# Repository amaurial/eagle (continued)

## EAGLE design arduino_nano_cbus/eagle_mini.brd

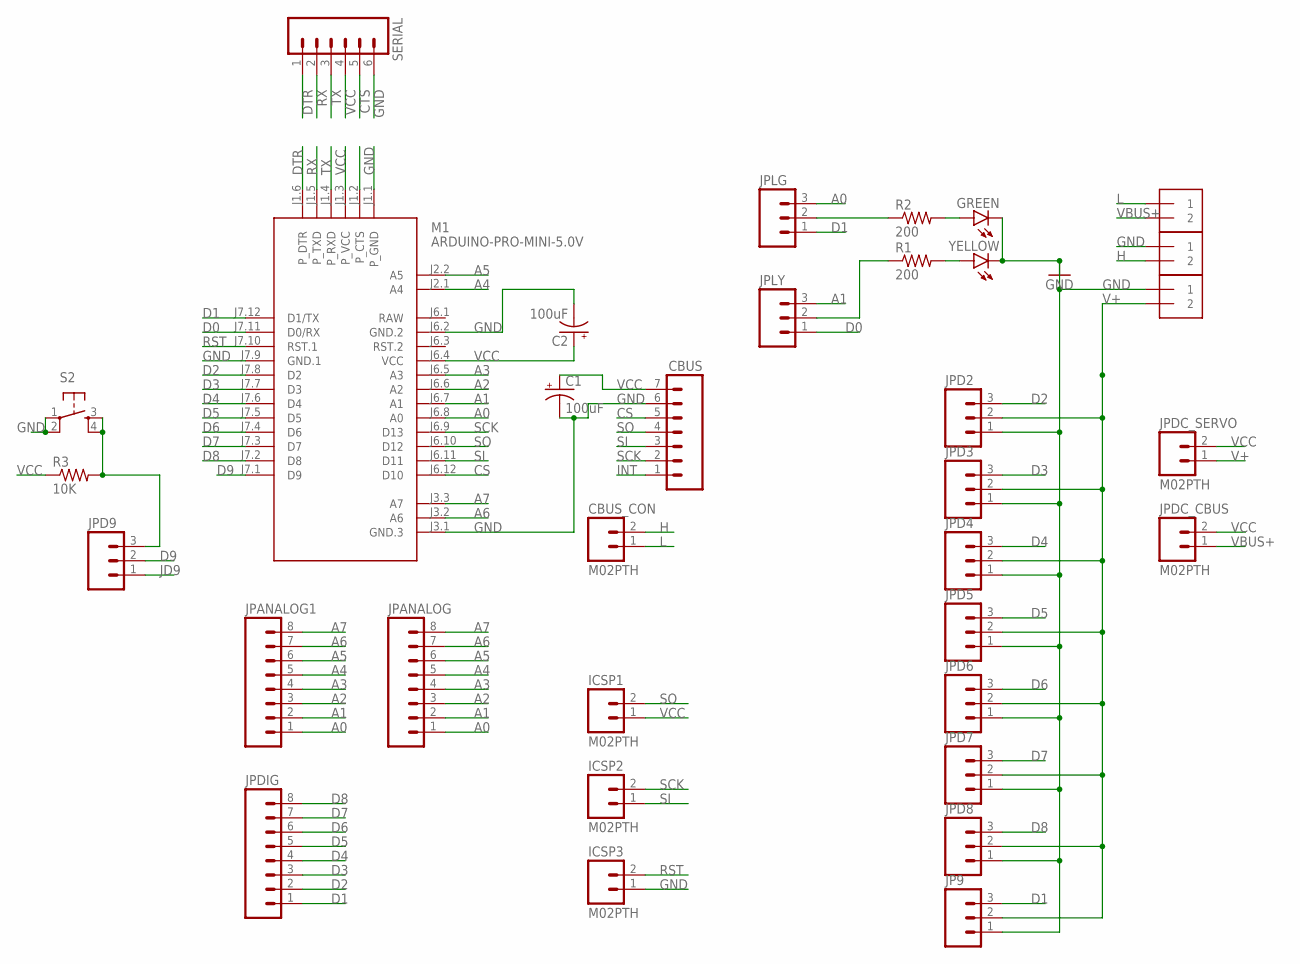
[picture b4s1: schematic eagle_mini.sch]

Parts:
C1, C2: 100uF; E2,5-6
CBUS: M07; 1X07
CBUS_CON: M02PTH; 1X02
EXT_VCC: 1X2-3.5MM
GREEN: LED-3MM-NO_SILK; LED3MM-NS
ICSP1, ICSP2, ICSP3: M02PTH; 1X02
J1, J2: 1X2-3.5MM
JP9: M03PTH; 1X03
JPANALOG, JPANALOG1: M08; 1X08_ROUND
JPD2, JPD3, JPD4, JPD5, JPD6, JPD7, JPD8, JPD9: M03PTH; 1X03
JPDC_CBUS: M02PTH; 1X02
JPDC_SERVO: M02PTH; 1X02
JPDIG: M08; 1X08_ROUND
JPLG: M03PTH; 1X03
JPLY: M03PTH; 1X03
M1: ARDUINO-PRO-MINI-5.0V; ARDUINO-PRO-MINI
R1, R2: 200; AXIAL-0.3
R3: 10K; AXIAL-0.3
S2: TAC_SWITCHPTH; TACTILE-PTH
SERIAL: M06SILK_FEMALE_PTH; 1X06
YELLOW: LED-3MM-NO_SILK; LED3MM-NS

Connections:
A0: JPANALOG.1, JPANALOG1.1, JPLG.3, M1.J6.8 (A0)
A1: JPANALOG.2, JPANALOG1.2, JPLY.3, M1.J6.7 (A1)
A2: JPANALOG.3, JPANALOG1.3, M1.J6.6 (A2)
A3: JPANALOG.4, JPANALOG1.4, M1.J6.5 (A3)
A4: JPANALOG.5, JPANALOG1.5, M1.J2.1 (A4)
A5: JPANALOG.6, JPANALOG1.6, M1.J2.2 (A5)
A6: JPANALOG.7, JPANALOG1.7, M1.J3.2 (A6)
A7: JPANALOG.8, JPANALOG1.8, M1.J3.3 (A7)
CS: CBUS.5, M1.J6.12 (D10)
CTS: SERIAL.5
D0: JPLY.1, M1.J7.11 (D0/RX)
D1: JP9.3, JPDIG.1, JPLG.1, M1.J7.12 (D1/TX)
D2: JPD2.3, JPDIG.2, M1.J7.8 (D2)
D3: JPD3.3, JPDIG.3, M1.J7.7 (D3)
D4: JPD4.3, JPDIG.4, M1.J7.6 (D4)
D5: JPD5.3, JPDIG.5, M1.J7.5 (D5)
D6: JPD6.3, JPDIG.6, M1.J7.4 (D6)
D7: JPD7.3, JPDIG.7, M1.J7.3 (D7)
D8: JPD8.3, JPDIG.8, M1.J7.2 (D8)
D9: JPD9.2, M1.J7.1 (D9)
DTR: M1.J1.6 (P_DTR), SERIAL.1
GND: C1.-, C2.-, CBUS.6, EXT_VCC.1, GREEN.K (C), ICSP3.1, J1.1, JP9.1, JPD2.1, JPD3.1, JPD4.1, JPD5.1, JPD6.1, JPD7.1, JPD8.1, M1.J1.1 (P_GND), M1.J3.1 (GND.3), M1.J6.2 (GND.2), M1.J7.9 (GND.1), S2.1, S2.2, SERIAL.6, YELLOW.K (C)
H: CBUS_CON.2, J1.2
INT: CBUS.1
JD9: JPD9.1
L: CBUS_CON.1, J2.1
unnamed: JPD9.3, R3.P$2 (2), S2.3, S2.4
unnamed: GREEN.A, R2.P$2 (2)
unnamed: R1.P$2 (2), YELLOW.A
unnamed: JPLG.2, R2.P$1 (1)
unnamed: JPLY.2, R1.P$1 (1)
RAW: M1.J6.1 (RAW)
RST: ICSP3.2, M1.J7.10 (RST.1)
RX: M1.J1.5 (P_TXD), SERIAL.2
SCK: CBUS.2, ICSP2.2, M1.J6.9 (D13)
SI: CBUS.3, ICSP2.1, M1.J6.11 (D11)
SO: CBUS.4, ICSP1.2, M1.J6.10 (D12)
TX: M1.J1.4 (P_RXD), SERIAL.3
V+: EXT_VCC.2, JP9.2, JPD2.2, JPD3.2, JPD4.2, JPD5.2, JPD6.2, JPD7.2, JPD8.2, JPDC_SERVO.1
VBUS+: J2.2, JPDC_CBUS.1
VCC: C1.+, C2.+, CBUS.7, ICSP1.1, JPDC_CBUS.2, JPDC_SERVO.2, M1.J1.3 (P_VCC), M1.J6.4 (VCC), R3.P$1 (1), SERIAL.4

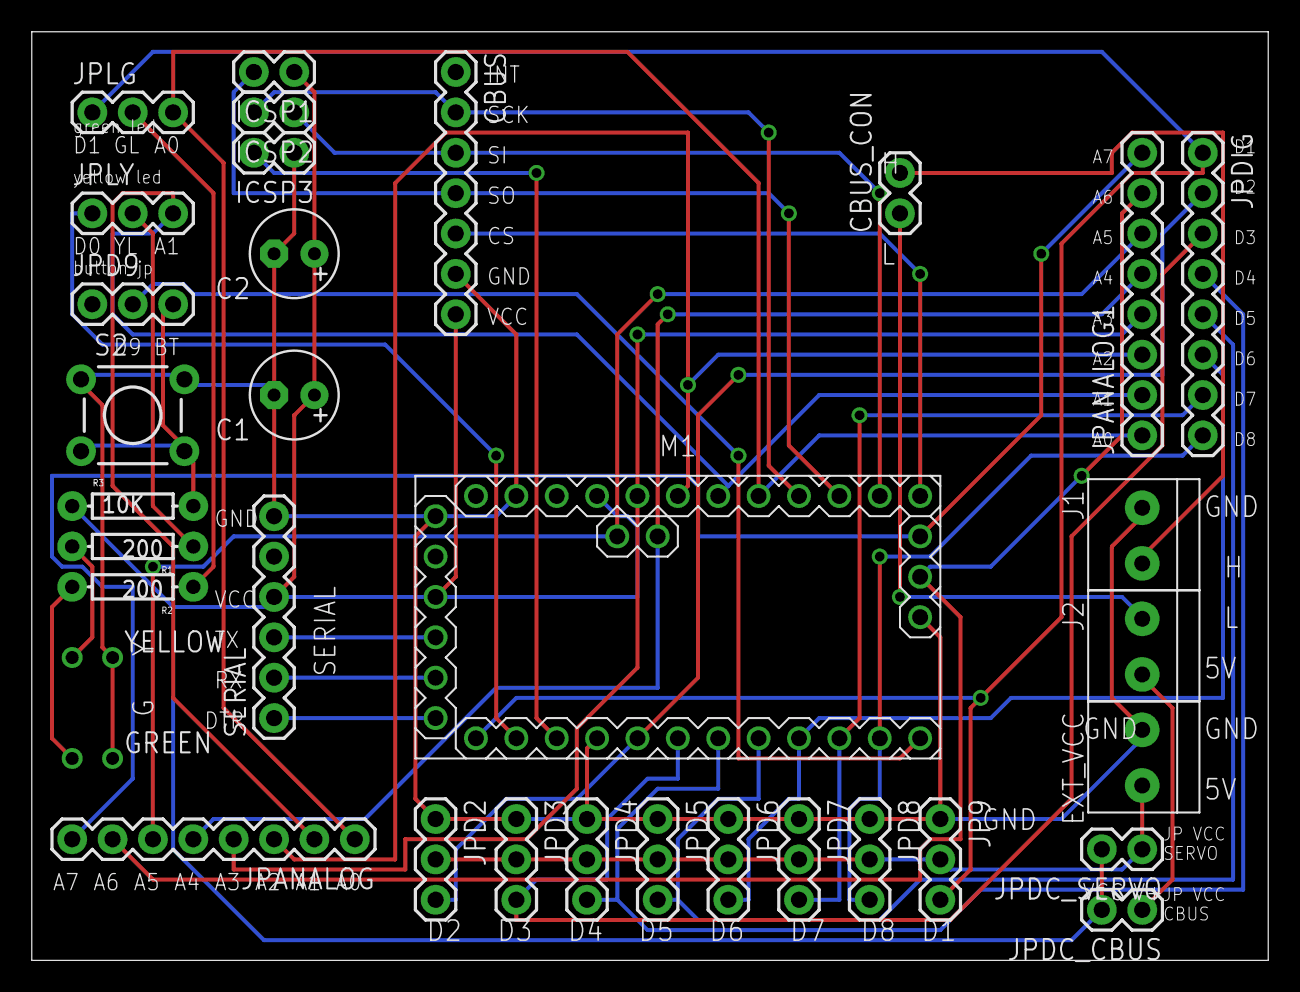
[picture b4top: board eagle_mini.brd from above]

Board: 2 copper layers, 77.8 x 58.4 mm, 34 parts (0 on the bottom side), 37 nets.

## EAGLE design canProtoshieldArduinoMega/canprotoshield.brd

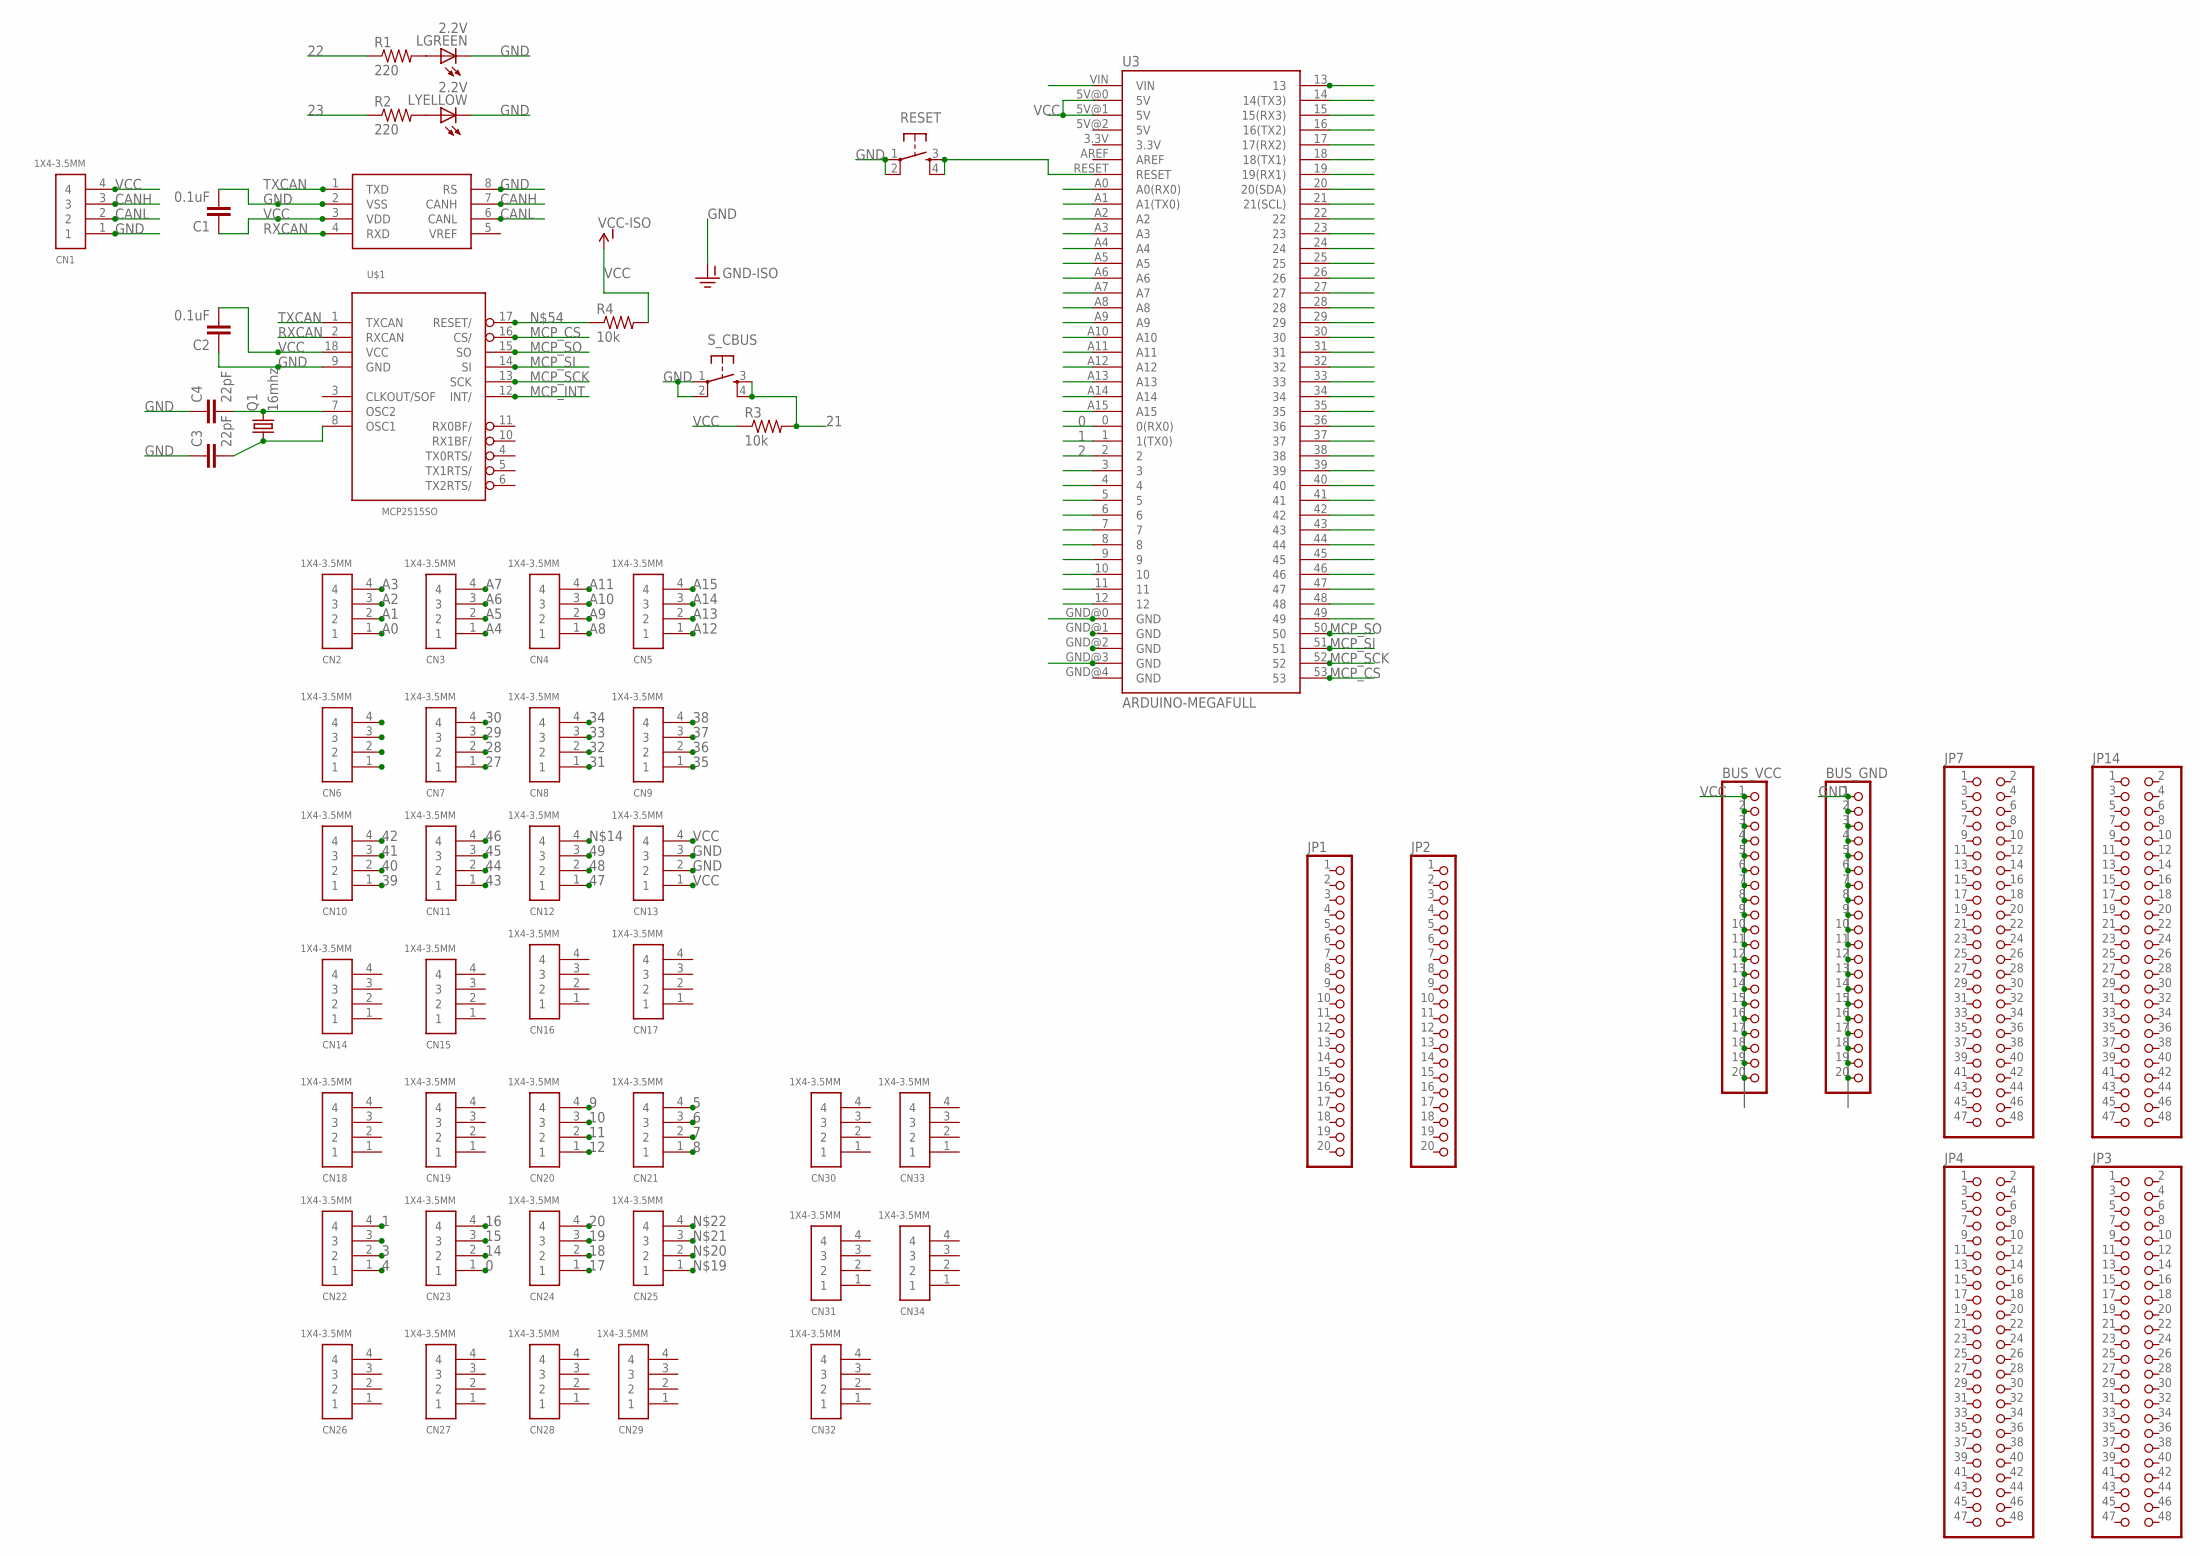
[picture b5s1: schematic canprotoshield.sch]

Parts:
BUS_GND: PINHD-1X20; 1X20
BUS_VCC: PINHD-1X20; 1X20
C1, C2: 0.1uF; 0805
C3, C4: 22pF; 0805
CN1, CN2, CN3, CN4, CN5, CN6, CN7, CN8, CN9, CN10, CN11, CN12, CN13, CN14, CN15, CN16, CN17, CN18, CN19, CN20, CN21, CN22, CN23, CN24, CN25, CN26, CN27, CN28, CN29, CN30, CN31, CN32, CN33, CN34: 1X4-3.5MM; 1X04-3.5MM
JP1, JP2: PINHD-1X20-BIG; 1X20-BIG
JP3, JP4, JP7, JP14: PINHD-2X24; 2X24
LGREEN: 2.2V; LED3MM
LYELLOW: 2.2V; LED3MM
Q1: 16mhz; HC49/S
R1, R2: 220; M2012
R3, R4: 10k; M2012
RESET: TAC_SWITCHPTH; TACTILE-PTH
S_CBUS: TAC_SWITCHPTH; TACTILE-PTH
U2: MCP2551; SO08
U3: ARDUINO-MEGAFULL; ARDUINO_MEGA
U$1: MCP2515SO; SO18L

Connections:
0: CN23.1, U3.0 (0(RX0))
1: CN22.4, U3.1 (1(TX0))
2: CN22.3, U3.2
3: CN22.2, U3.3
4: CN22.1, U3.4
5: CN21.4, U3.5
6: CN21.3, U3.6
7: CN21.2, U3.7
8: CN21.1, U3.8
9: CN20.4, U3.9
10: CN20.3, U3.10
11: CN20.2, U3.11
12: CN20.1, U3.12
13: U3.13
14: CN23.2, U3.14 (14(TX3))
15: CN23.3, U3.15 (15(RX3))
16: CN23.4, U3.16 (16(TX2))
17: CN24.1, U3.17 (17(RX2))
18: CN24.2, U3.18 (18(TX1))
19: CN24.3, U3.19 (19(RX1))
20: CN24.4, U3.20 (20(SDA))
21: R3.2, S_CBUS.3, S_CBUS.4, U3.21 (21(SCL))
22: R1.1, U3.22
23: R2.1, U3.23
24: CN6.3, U3.24
25: CN6.2, U3.25
26: CN6.1, U3.26
27: CN7.1, U3.27
28: CN7.2, U3.28
29: CN7.3, U3.29
30: CN7.4, U3.30
31: CN8.1, U3.31
32: CN8.2, U3.32
33: CN8.3, U3.33
34: CN8.4, U3.34
35: CN9.1, U3.35
36: CN9.2, U3.36
37: CN9.3, U3.37
38: CN9.4, U3.38
39: CN10.1, U3.39
40: CN10.2, U3.40
41: CN10.3, U3.41
42: CN10.4, U3.42
43: CN11.1, U3.43
44: CN11.2, U3.44
45: CN11.3, U3.45
46: CN11.4, U3.46
47: CN12.1, U3.47
48: CN12.2, U3.48
49: CN12.3, U3.49
A0: CN2.1, U3.A0 (A0(RX0))
A1: CN2.2, U3.A1 (A1(TX0))
A2: CN2.3, U3.A2
A3: CN2.4, U3.A3
A4: CN3.1, U3.A4
A5: CN3.2, U3.A5
A6: CN3.3, U3.A6
A7: CN3.4, U3.A7
A8: CN4.1, U3.A8
A9: CN4.2, U3.A9
A10: CN4.3, U3.A10
A11: CN4.4, U3.A11
A12: CN5.1, U3.A12
A13: CN5.2, U3.A13
A14: CN5.3, U3.A14
A15: CN5.4, U3.A15
CANH: CN1.3, U2.7 (CANH)
CANL: CN1.2, U2.6 (CANL)
GND: BUS_GND.1, C1.2, C2.1, C3.1, C4.1, CN1.1, CN13.2, CN13.3, LGREEN.K (C), LYELLOW.K (C), RESET.1, RESET.2, S_CBUS.1, S_CBUS.2, U2.8 (RS), U3.GND@0 (GND), U3.GND@3 (GND), U$1.9 (GND)
MCP_CS: U3.53, U$1.16 (CS/)
MCP_INT: U$1.12 (INT/)
MCP_SCK: U3.52, U$1.13 (SCK)
MCP_SI: U3.51, U$1.14 (SI)
MCP_SO: U3.50, U$1.15 (SO)
unnamed: C4.2, Q1.2, U$1.7 (OSC2)
unnamed: C3.2, Q1.1, U$1.8 (OSC1)
unnamed: LYELLOW.A, R2.2
unnamed: LGREEN.A, R1.2
unnamed: RESET.3, RESET.4, U3.RESET
unnamed: R4.1, U$1.17 (RESET/)
RXCAN: U2.4 (RXD), U$1.2 (RXCAN)
TXCAN: U2.1 (TXD), U$1.1 (TXCAN)
VCC: C1.1, C2.2, CN1.4, CN13.1, CN13.4, R3.1, R4.2, U3.5V@0 (5V), U3.5V@1 (5V), U$1.18 (VCC)
VIN: U3.VIN

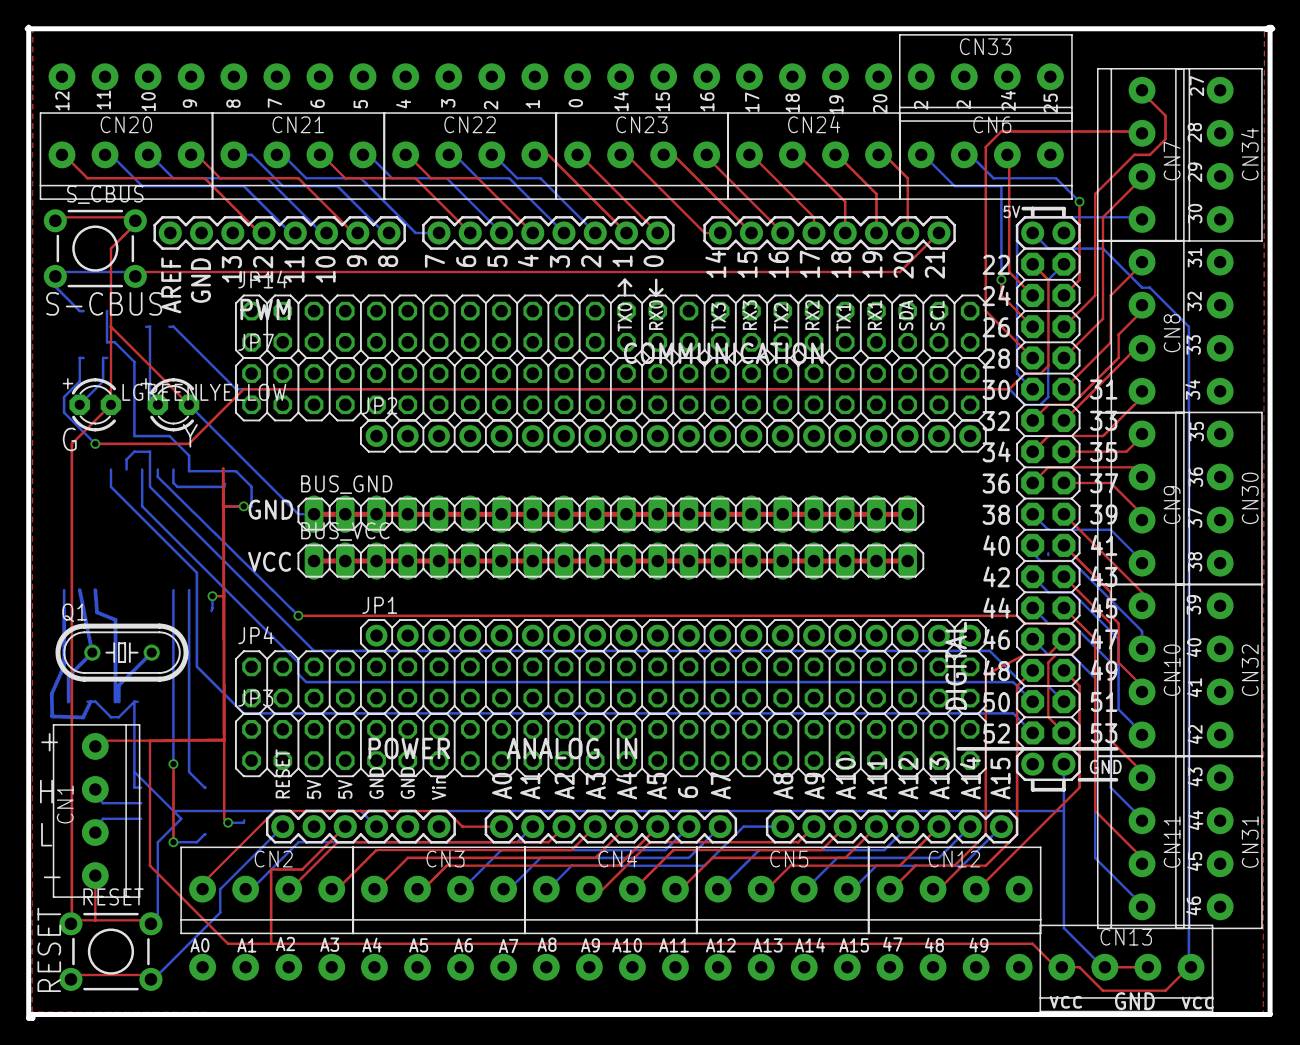
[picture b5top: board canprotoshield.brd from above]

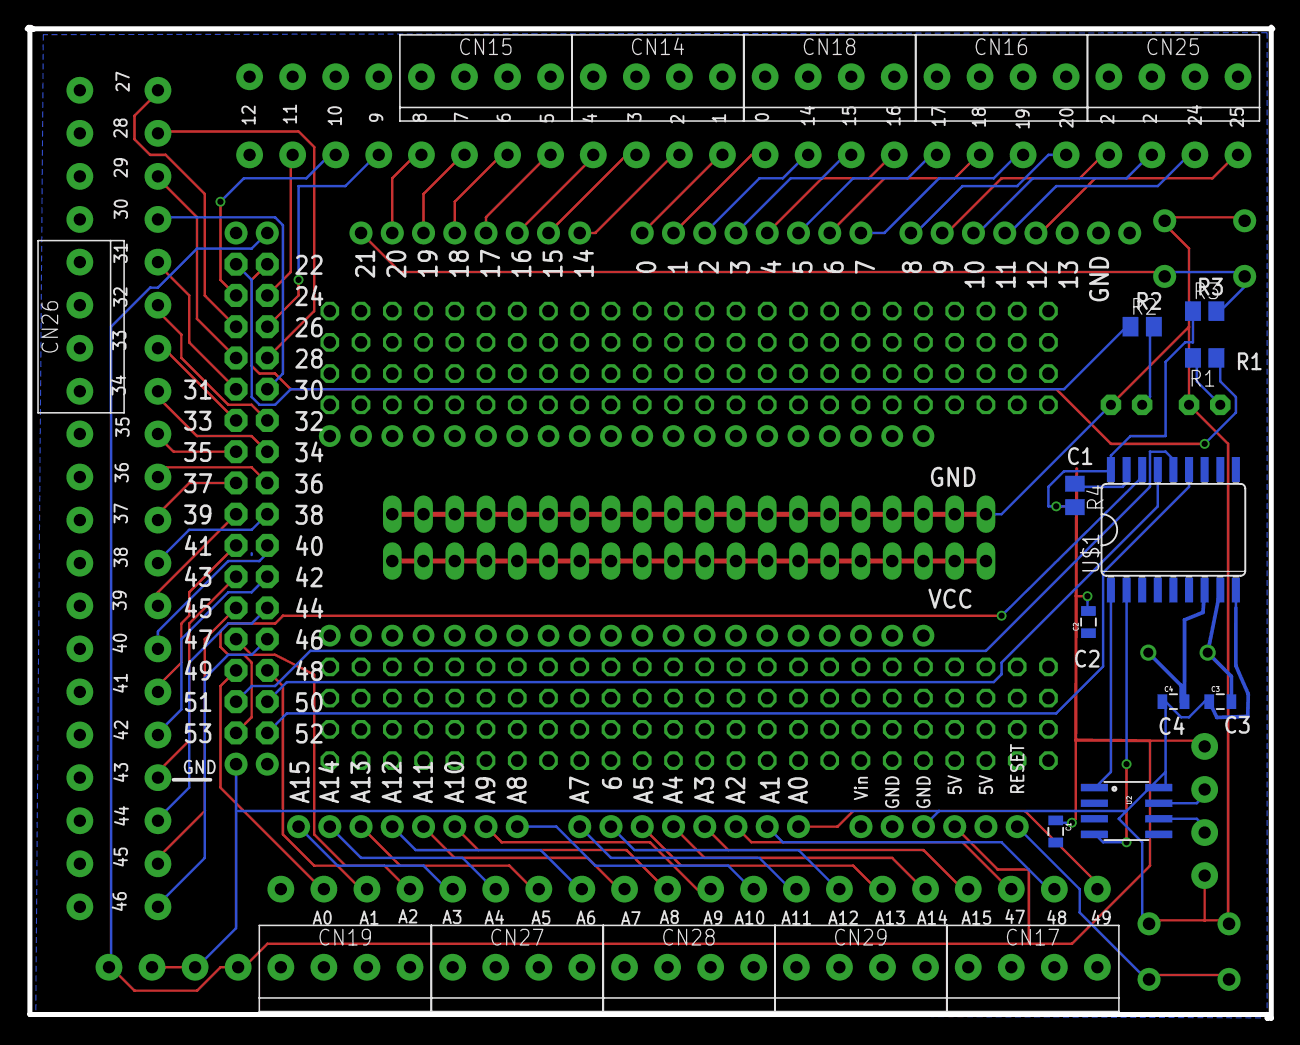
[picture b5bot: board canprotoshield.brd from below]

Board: 2 copper layers, 101.3 x 80.6 mm, 58 parts (21 on the bottom side), 81 nets.

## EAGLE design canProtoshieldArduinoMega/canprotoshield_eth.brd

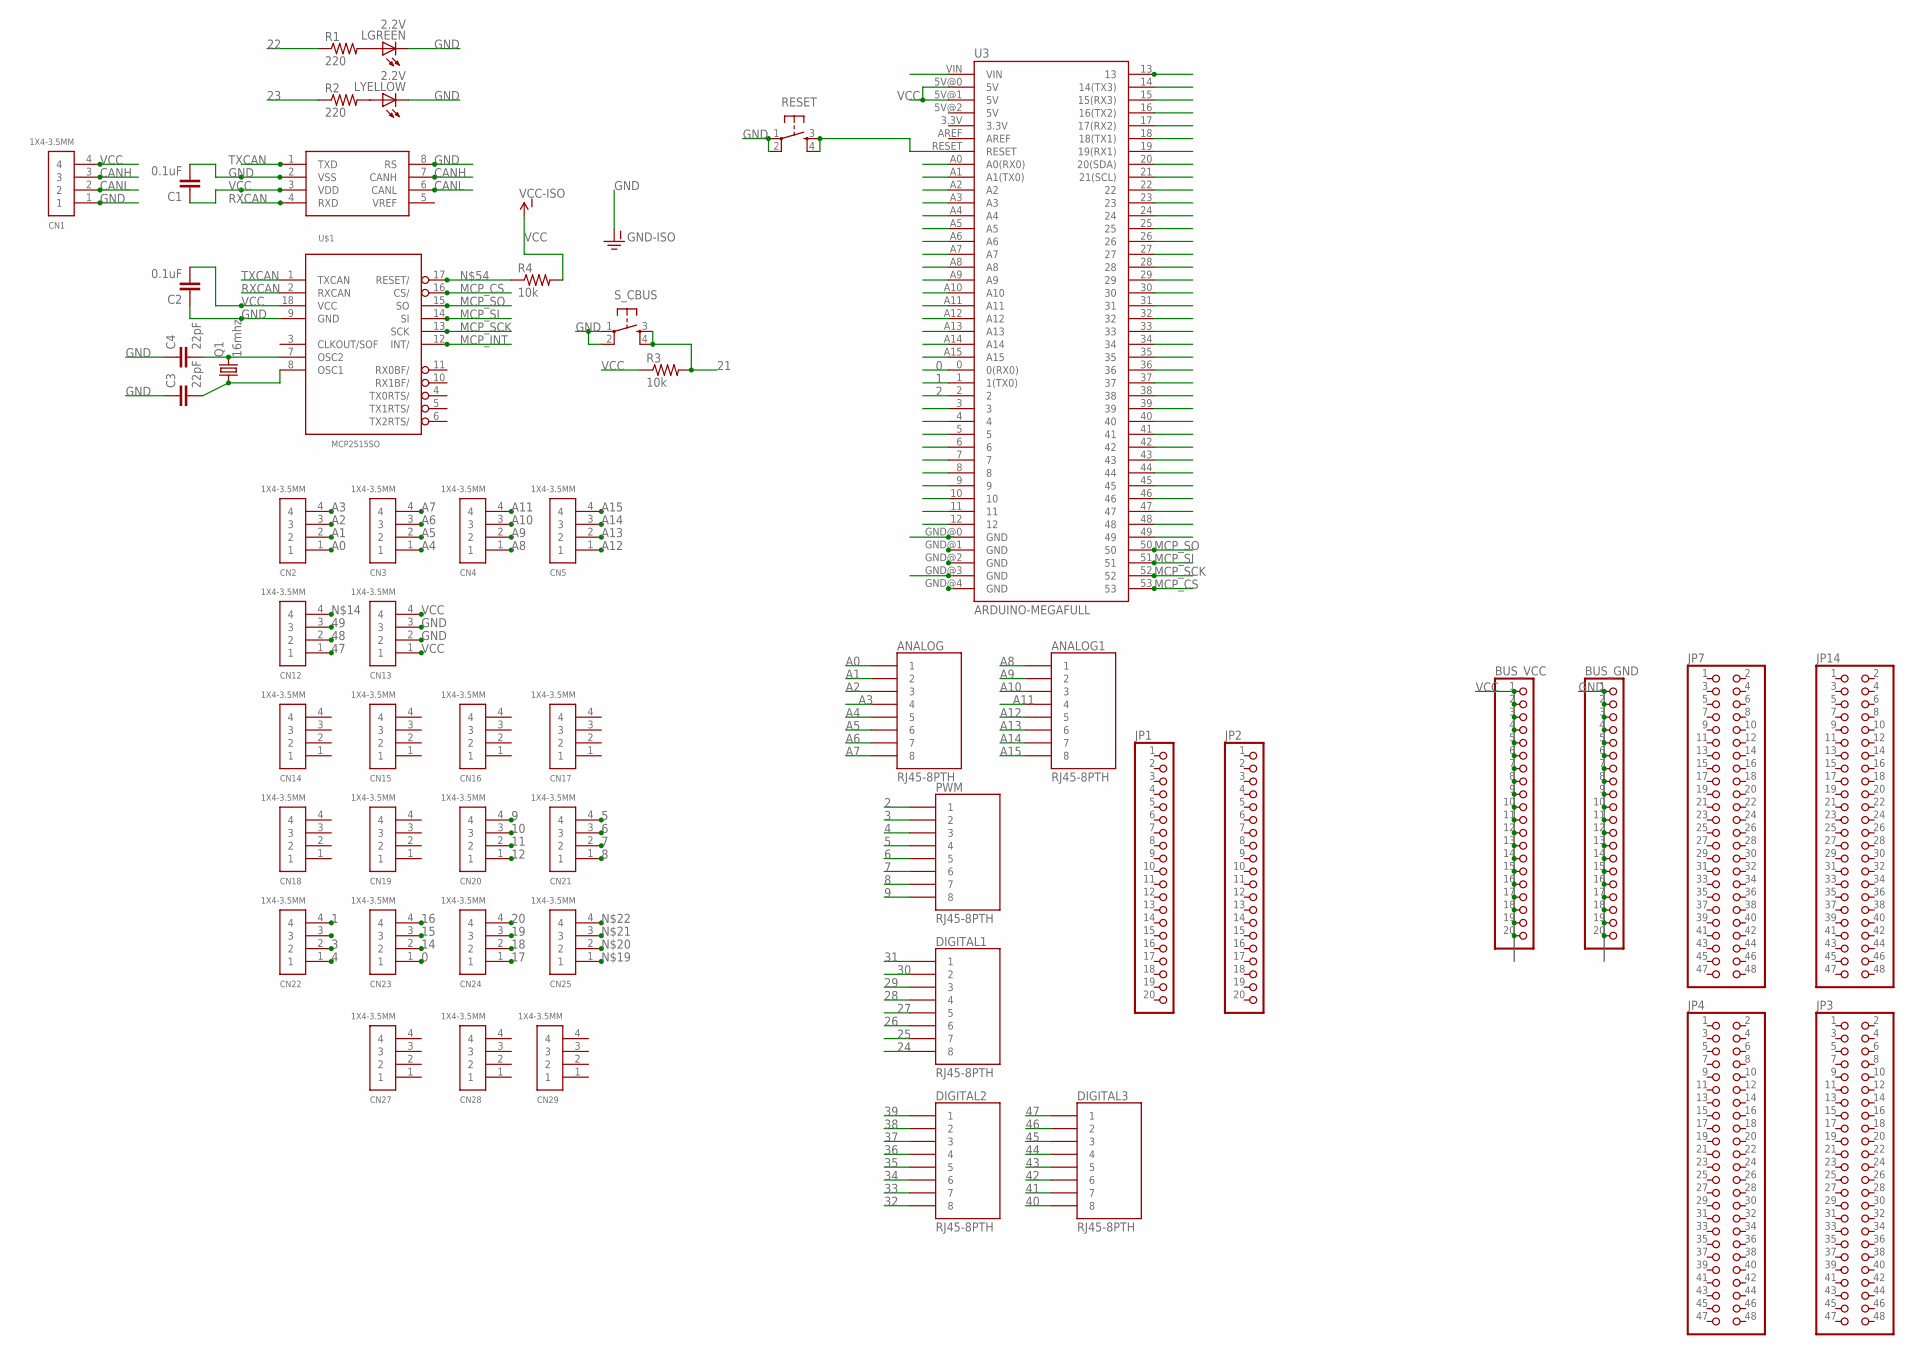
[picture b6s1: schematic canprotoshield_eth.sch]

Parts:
ANALOG, ANALOG1: RJ45-8PTH; RJ45-8
BUS_GND: PINHD-1X20; 1X20
BUS_VCC: PINHD-1X20; 1X20
C1, C2: 0.1uF; 0805
C3, C4: 22pF; 0805
CN1, CN2, CN3, CN4, CN5, CN12, CN13, CN14, CN15, CN16, CN17, CN18, CN19, CN20, CN21, CN22, CN23, CN24, CN25, CN27, CN28, CN29: 1X4-3.5MM; 1X04-3.5MM
DIGITAL1, DIGITAL2, DIGITAL3: RJ45-8PTH; RJ45-8
JP1, JP2: PINHD-1X20-BIG; 1X20-BIG
JP3, JP4, JP7, JP14: PINHD-2X24; 2X24
LGREEN: 2.2V; LED3MM
LYELLOW: 2.2V; LED3MM
PWM: RJ45-8PTH; RJ45-8
Q1: 16mhz; HC49/S
R1, R2: 220; M2012
R3, R4: 10k; M2012
RESET: TAC_SWITCHPTH; TACTILE-PTH
S_CBUS: TAC_SWITCHPTH; TACTILE-PTH
U2: MCP2551; SO08
U3: ARDUINO-MEGAFULL; ARDUINO_MEGA
U$1: MCP2515SO; SO18L

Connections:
0: CN23.1, U3.0 (0(RX0))
1: CN22.4, U3.1 (1(TX0))
2: CN22.3, PWM.1, U3.2
3: CN22.2, PWM.2, U3.3
4: CN22.1, PWM.3, U3.4
5: CN21.4, PWM.4, U3.5
6: CN21.3, PWM.5, U3.6
7: CN21.2, PWM.6, U3.7
8: CN21.1, PWM.7, U3.8
9: CN20.4, PWM.8, U3.9
10: CN20.3, U3.10
11: CN20.2, U3.11
12: CN20.1, U3.12
13: U3.13
14: CN23.2, U3.14 (14(TX3))
15: CN23.3, U3.15 (15(RX3))
16: CN23.4, U3.16 (16(TX2))
17: CN24.1, U3.17 (17(RX2))
18: CN24.2, U3.18 (18(TX1))
19: CN24.3, U3.19 (19(RX1))
20: CN24.4, U3.20 (20(SDA))
21: R3.2, S_CBUS.3, S_CBUS.4, U3.21 (21(SCL))
22: R1.1, U3.22
23: R2.1, U3.23
24: DIGITAL1.8, U3.24
25: DIGITAL1.7, U3.25
26: DIGITAL1.6, U3.26
27: DIGITAL1.5, U3.27
28: DIGITAL1.4, U3.28
29: DIGITAL1.3, U3.29
30: DIGITAL1.2, U3.30
31: DIGITAL1.1, U3.31
32: DIGITAL2.8, U3.32
33: DIGITAL2.7, U3.33
34: DIGITAL2.6, U3.34
35: DIGITAL2.5, U3.35
36: DIGITAL2.4, U3.36
37: DIGITAL2.3, U3.37
38: DIGITAL2.2, U3.38
39: DIGITAL2.1, U3.39
40: DIGITAL3.8, U3.40
41: DIGITAL3.7, U3.41
42: DIGITAL3.6, U3.42
43: DIGITAL3.5, U3.43
44: DIGITAL3.4, U3.44
45: DIGITAL3.3, U3.45
46: DIGITAL3.2, U3.46
47: CN12.1, DIGITAL3.1, U3.47
48: CN12.2, U3.48
49: CN12.3, U3.49
A0: ANALOG.1, CN2.1, U3.A0 (A0(RX0))
A1: ANALOG.2, CN2.2, U3.A1 (A1(TX0))
A2: ANALOG.3, CN2.3, U3.A2
A3: ANALOG.4, CN2.4, U3.A3
A4: ANALOG.5, CN3.1, U3.A4
A5: ANALOG.6, CN3.2, U3.A5
A6: ANALOG.7, CN3.3, U3.A6
A7: ANALOG.8, CN3.4, U3.A7
A8: ANALOG1.1, CN4.1, U3.A8
A9: ANALOG1.2, CN4.2, U3.A9
A10: ANALOG1.3, CN4.3, U3.A10
A11: ANALOG1.4, CN4.4, U3.A11
A12: ANALOG1.5, CN5.1, U3.A12
A13: ANALOG1.6, CN5.2, U3.A13
A14: ANALOG1.7, CN5.3, U3.A14
A15: ANALOG1.8, CN5.4, U3.A15
CANH: CN1.3, U2.7 (CANH)
CANL: CN1.2, U2.6 (CANL)
GND: BUS_GND.1, C1.2, C2.1, C3.1, C4.1, CN1.1, CN13.2, CN13.3, LGREEN.K (C), LYELLOW.K (C), RESET.1, RESET.2, S_CBUS.1, S_CBUS.2, U2.8 (RS), U3.GND@0 (GND), U3.GND@3 (GND), U3.GND@4 (GND), U$1.9 (GND)
MCP_CS: U3.53, U$1.16 (CS/)
MCP_INT: U$1.12 (INT/)
MCP_SCK: U3.52, U$1.13 (SCK)
MCP_SI: U3.51, U$1.14 (SI)
MCP_SO: U3.50, U$1.15 (SO)
unnamed: C4.2, Q1.2, U$1.7 (OSC2)
unnamed: C3.2, Q1.1, U$1.8 (OSC1)
unnamed: LYELLOW.A, R2.2
unnamed: LGREEN.A, R1.2
unnamed: RESET.3, RESET.4, U3.RESET
unnamed: R4.1, U$1.17 (RESET/)
RXCAN: U2.4 (RXD), U$1.2 (RXCAN)
TXCAN: U2.1 (TXD), U$1.1 (TXCAN)
VCC: C1.1, C2.2, CN1.4, CN13.1, CN13.4, R3.1, R4.2, U3.5V@0 (5V), U3.5V@1 (5V), U$1.18 (VCC)
VIN: U3.VIN

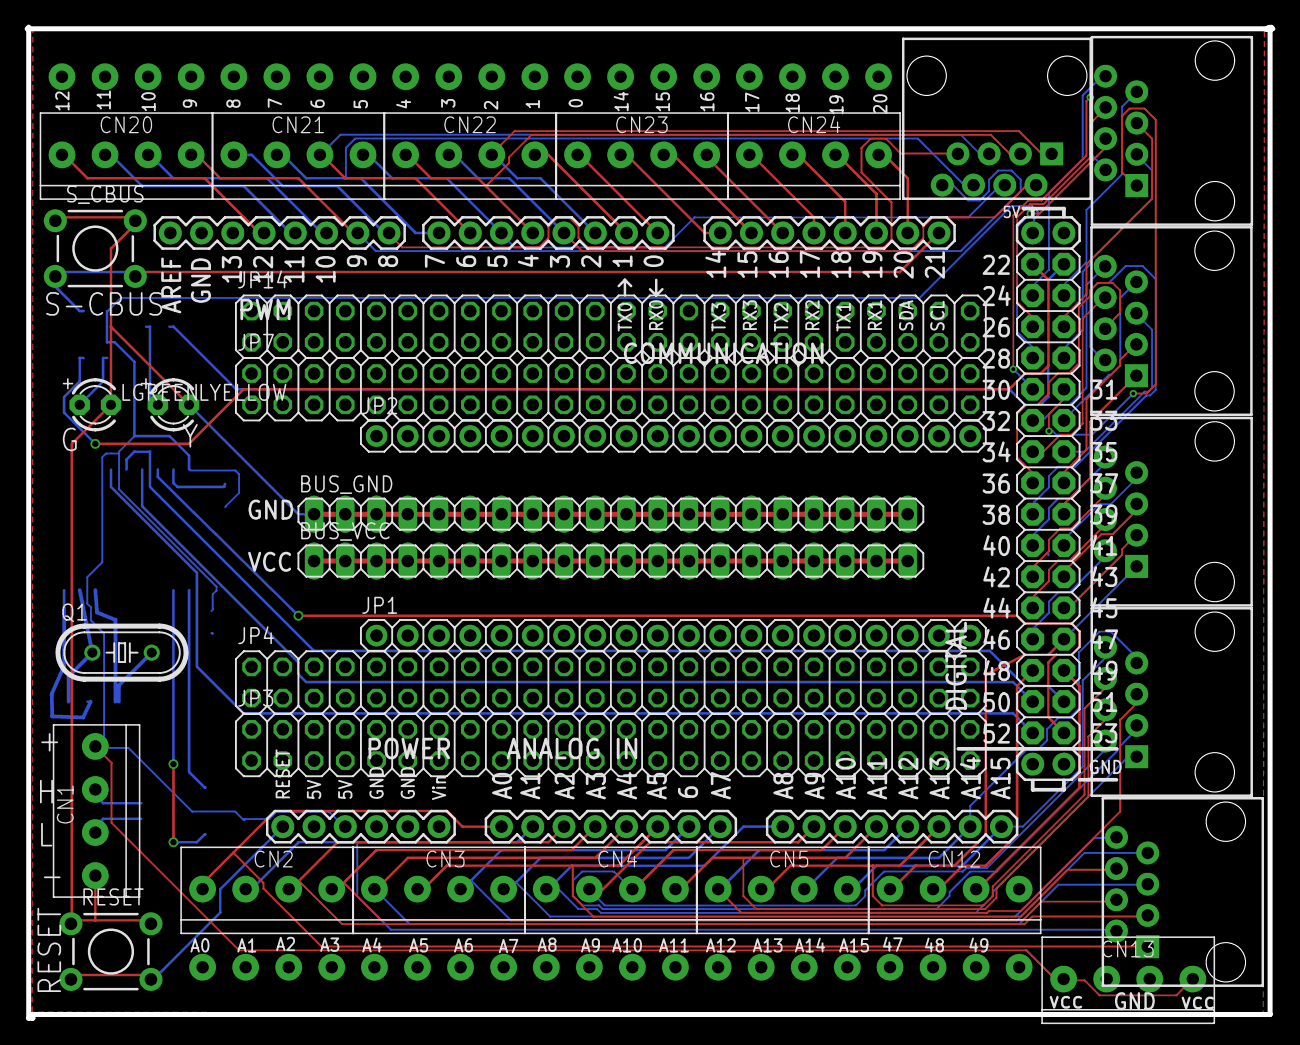
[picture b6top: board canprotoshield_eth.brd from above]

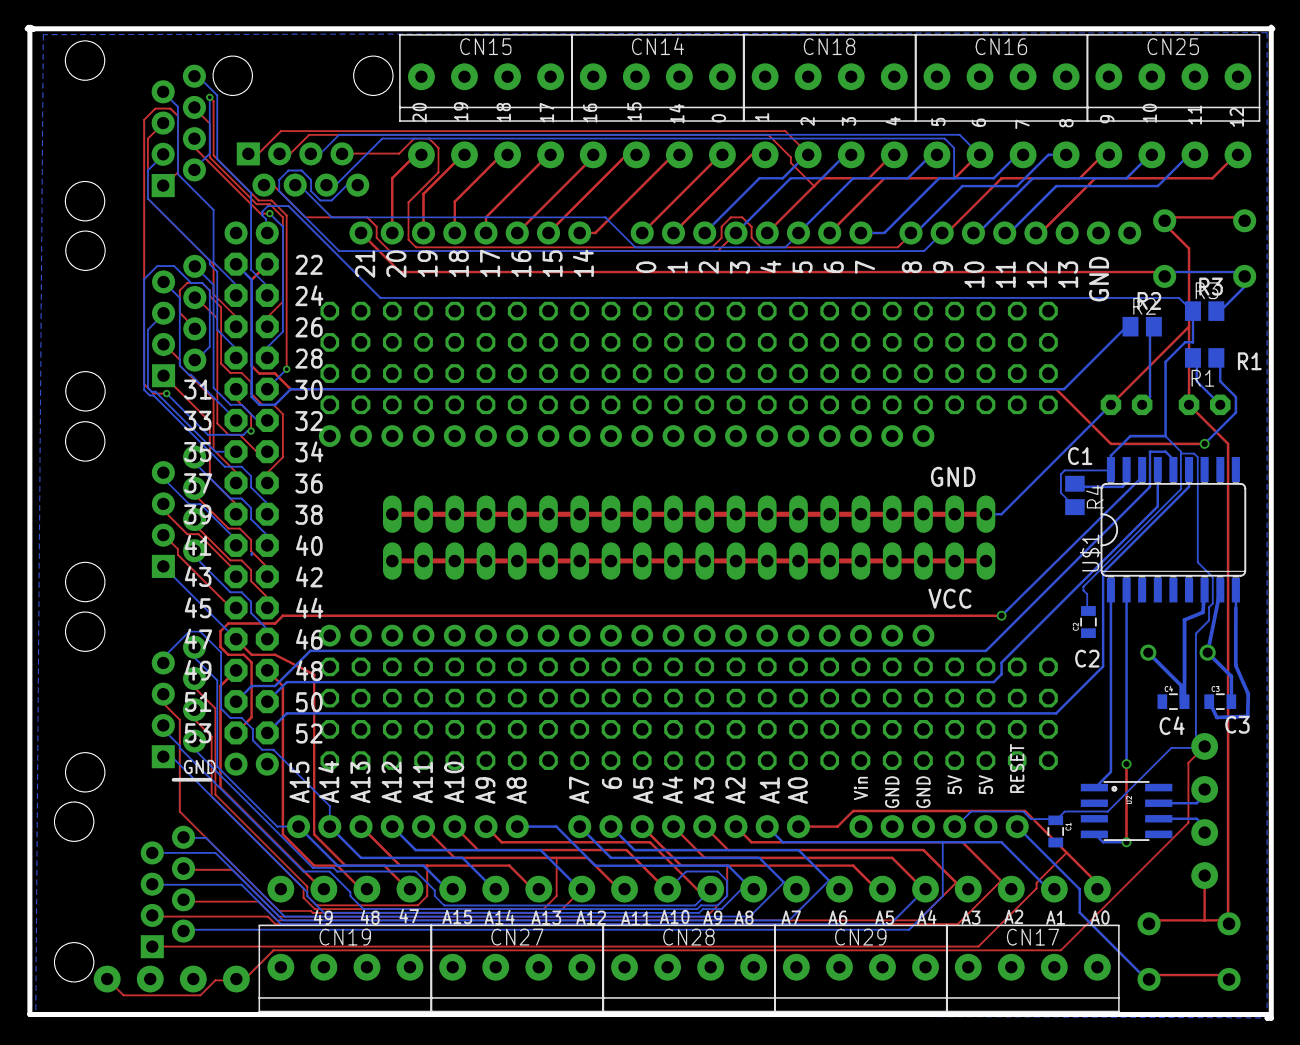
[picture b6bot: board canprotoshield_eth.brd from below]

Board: 2 copper layers, 101.3 x 80.6 mm, 52 parts (20 on the bottom side), 81 nets.

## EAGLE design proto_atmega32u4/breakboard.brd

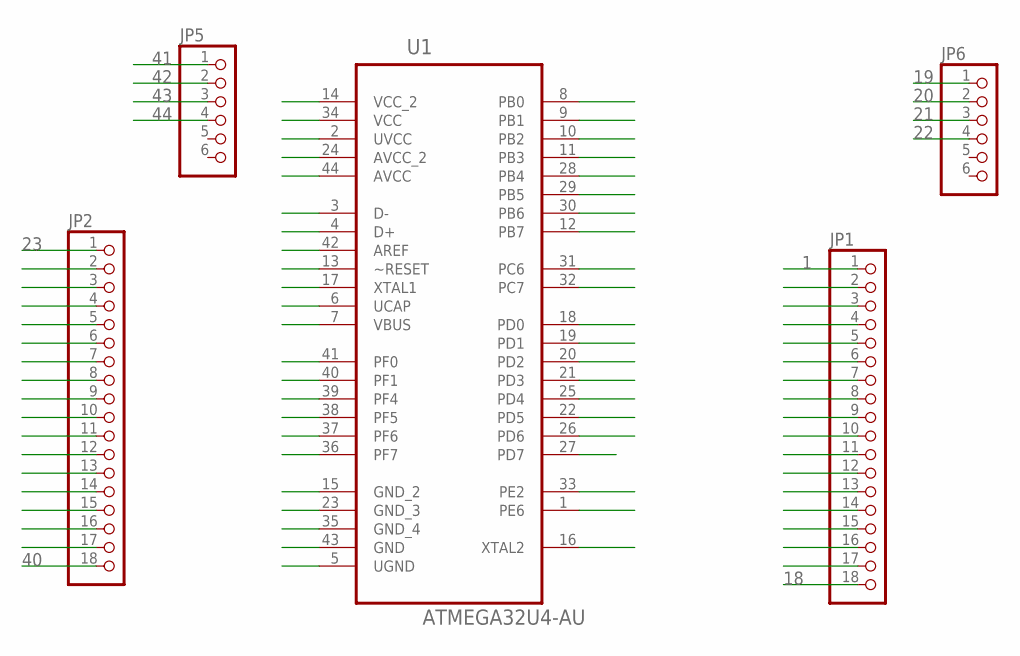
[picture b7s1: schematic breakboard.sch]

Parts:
JP1, JP2: PINHD-1X18-BIG; 1X18-BIG
JP5, JP6: PINHD-1X6; 1X06
U1: ATMEGA32U4-AU; QFP80P1200X1200X120-44N

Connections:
1: JP1.1, U1.1 (PE6)
2: JP1.2, U1.2 (UVCC)
3: JP1.3, U1.3 (D-)
4: JP1.4, U1.4 (D+)
5: JP1.5, U1.5 (UGND)
6: JP1.6, U1.6 (UCAP)
7: JP1.7, U1.7 (VBUS)
8: JP1.8, U1.8 (PB0)
9: JP1.9, U1.9 (PB1)
10: JP1.10, U1.10 (PB2)
11: JP1.11, U1.11 (PB3)
12: JP1.12, U1.12 (PB7)
13: JP1.13, U1.13 (~RESET)
14: JP1.14, U1.14 (VCC_2)
15: JP1.15, U1.15 (GND_2)
16: JP1.16, U1.16 (XTAL2)
17: JP1.17, U1.17 (XTAL1)
18: JP1.18, U1.18 (PD0)
19: JP6.1, U1.19 (PD1)
20: JP6.2, U1.20 (PD2)
21: JP6.3, U1.21 (PD3)
22: JP6.4, U1.22 (PD5)
23: JP2.1, U1.23 (GND_3)
24: JP2.2, U1.24 (AVCC_2)
25: JP2.3, U1.25 (PD4)
26: JP2.4, U1.26 (PD6)
27: JP2.5, U1.27 (PD7)
28: JP2.6, U1.28 (PB4)
29: JP2.7, U1.29 (PB5)
30: JP2.8, U1.30 (PB6)
31: JP2.9, U1.31 (PC6)
32: JP2.10, U1.32 (PC7)
33: JP2.11, U1.33 (PE2)
34: JP2.12, U1.34 (VCC)
35: JP2.13, U1.35 (GND_4)
36: JP2.14, U1.36 (PF7)
37: JP2.15, U1.37 (PF6)
38: JP2.16, U1.38 (PF5)
39: JP2.17, U1.39 (PF4)
40: JP2.18, U1.40 (PF1)
41: JP5.1, U1.41 (PF0)
42: JP5.2, U1.42 (AREF)
43: JP5.3, U1.43 (GND)
44: JP5.4, U1.44 (AVCC)

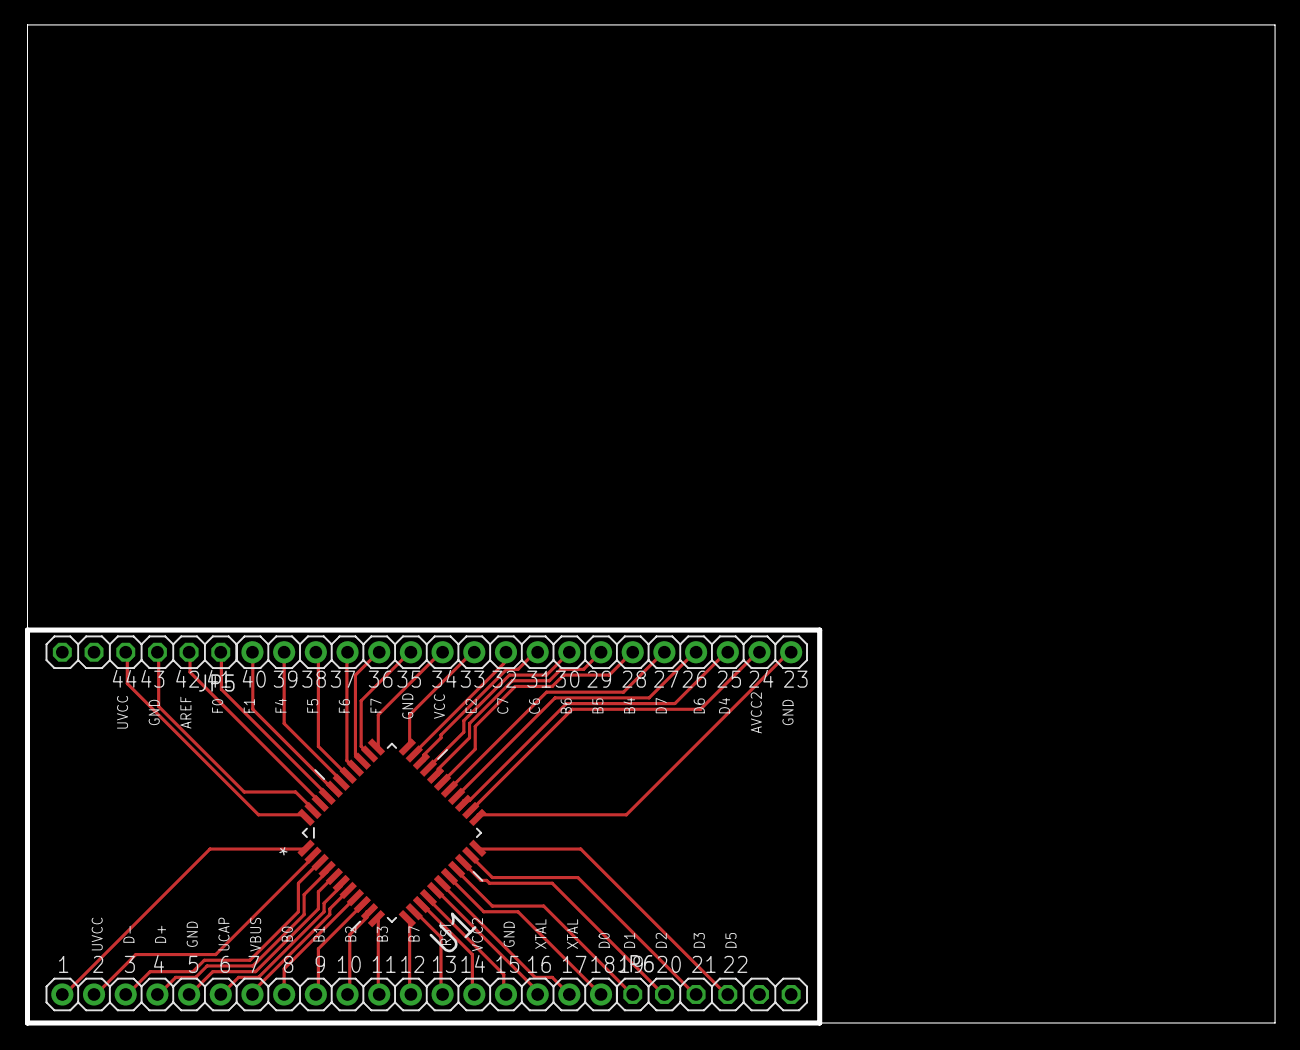
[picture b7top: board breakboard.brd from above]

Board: 2 copper layers, 100.0 x 80.0 mm, 5 parts (0 on the bottom side), 44 nets.
